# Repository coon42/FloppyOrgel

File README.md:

# FloppyOrgel
Collection of Software for the Floppy Orgel

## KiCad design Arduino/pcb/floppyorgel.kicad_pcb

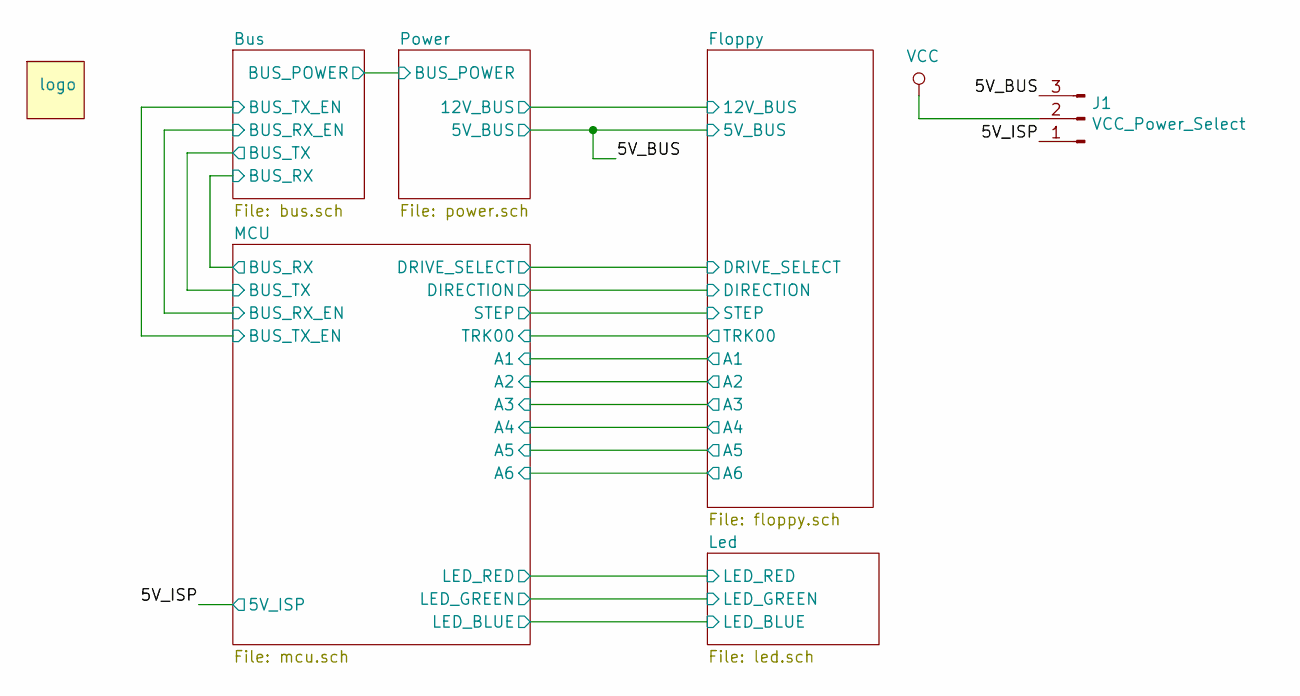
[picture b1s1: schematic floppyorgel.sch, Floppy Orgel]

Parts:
J1: VCC_Power_Select; switch_mmp122-r
L1: logo

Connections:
/5V_BUS: J1.3; also elsewhere on the board
/5V_ISP: J1.1; also elsewhere on the board
VCC: J1.2; also elsewhere on the board

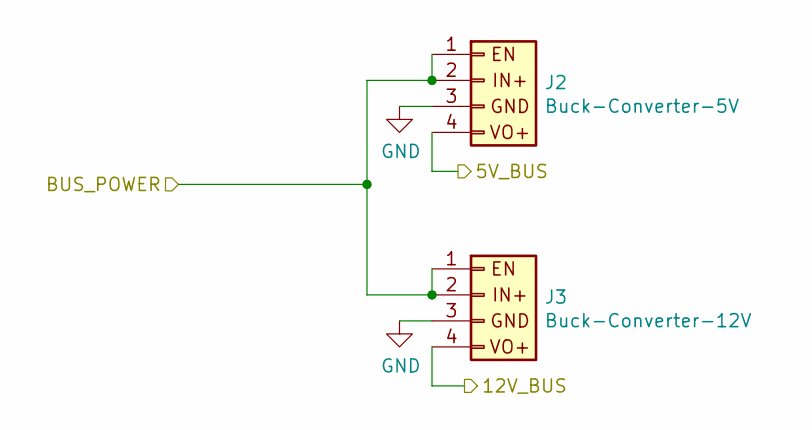
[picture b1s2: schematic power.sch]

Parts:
J2: Buck-Converter-5V; PinSocket_1x04_P2.54mm_Vertical
J3: Buck-Converter-12V; PinSocket_1x04_P2.54mm_Vertical

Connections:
/5V_BUS: J2.4; also elsewhere on the board
/Bus/BUS_POWER: J2.1, J2.2, J3.1, J3.2; also elsewhere on the board
/Floppy/12V_BUS: J3.4; also elsewhere on the board
GND: J2.3, J3.3; also elsewhere on the board

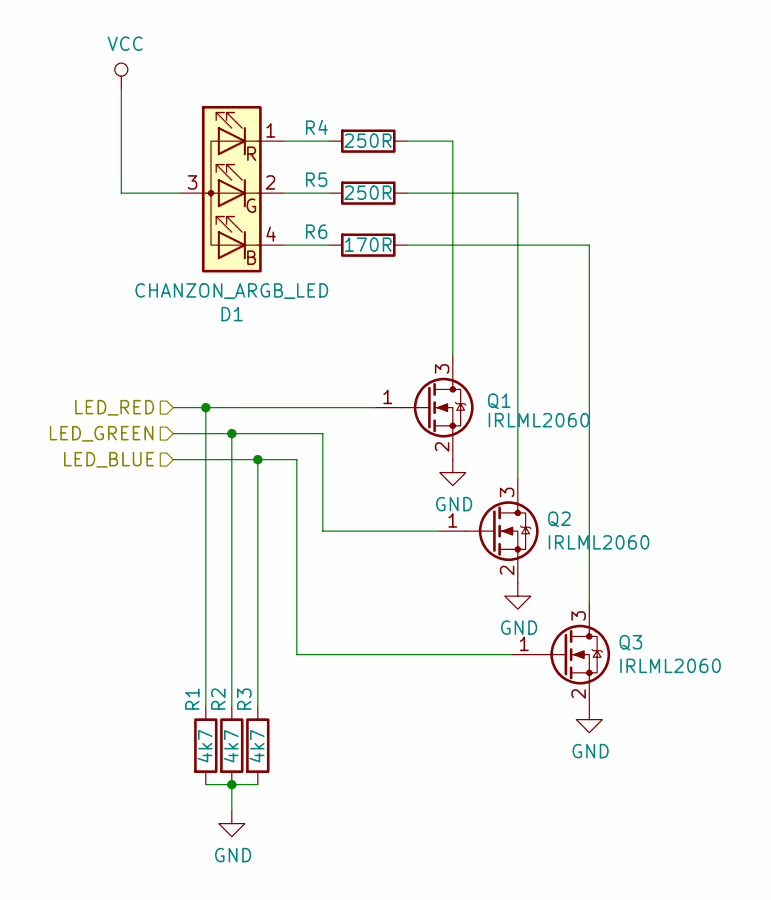
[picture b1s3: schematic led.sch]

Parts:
D1: CHANZON_ARGB_LED; rgb_led_0805_2012Metric
Q1, Q2, Q3: IRLML2060; SOT-23
R1, R2, R3: 4k7; R_0805_2012Metric
R4, R5: 250R; R_0805_2012Metric
R6: 170R; R_0805_2012Metric

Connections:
/Led/LED_BLUE: Q3.1 (G), R3.1; also elsewhere on the board
/Led/LED_GREEN: Q2.1 (G), R2.1; also elsewhere on the board
/Led/LED_RED: Q1.1 (G), R1.1; also elsewhere on the board
GND: Q1.2 (S), Q2.2 (S), Q3.2 (S), R1.2, R2.2, R3.2; also elsewhere on the board
unnamed: D1.1 (RK), R4.2
unnamed: D1.2 (GK), R5.2
unnamed: D1.4 (BK), R6.2
unnamed: Q1.3 (D), R4.1
unnamed: Q2.3 (D), R5.1
unnamed: Q3.3 (D), R6.1
VCC: D1.3 (COM); also elsewhere on the board

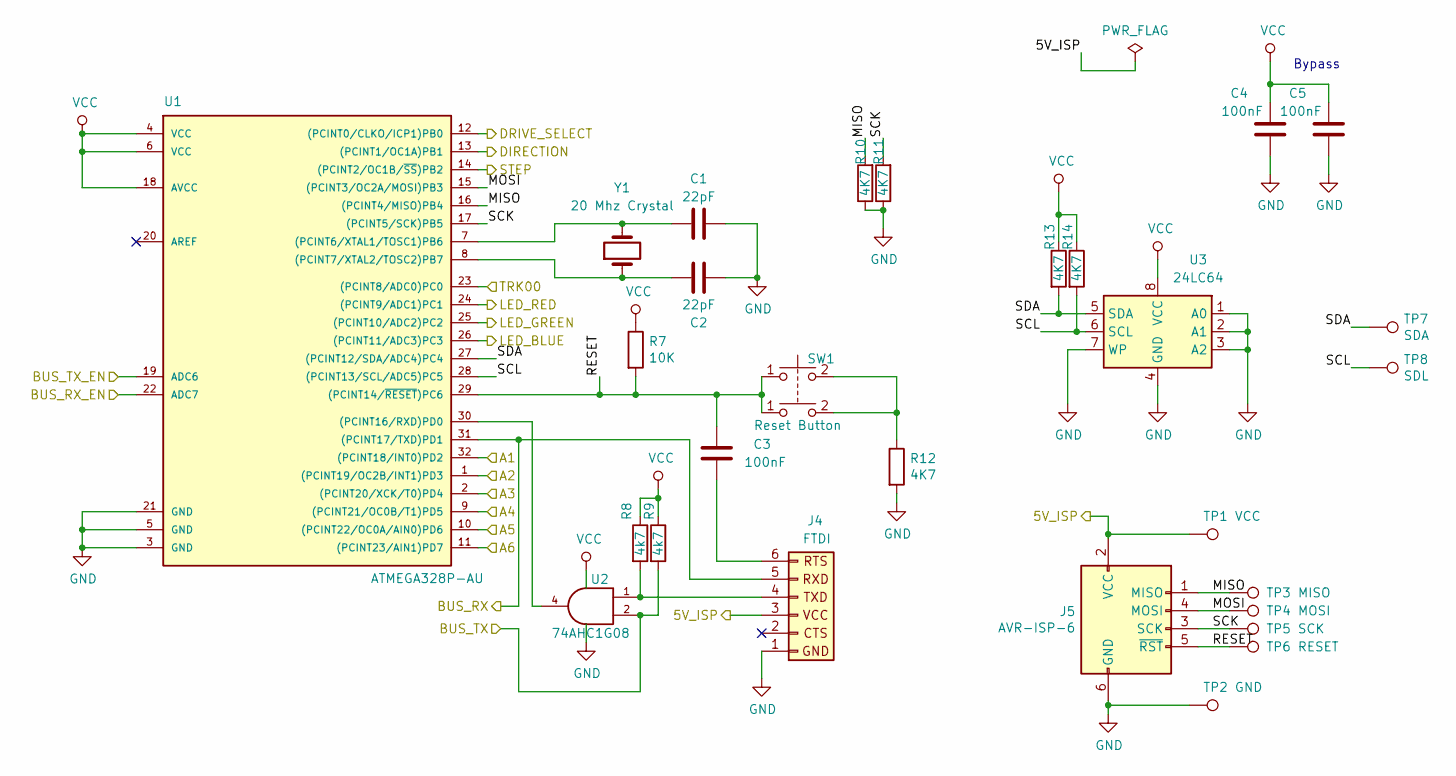
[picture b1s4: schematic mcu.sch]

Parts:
C1, C2: 22pF; C_0805_2012Metric
C3, C4, C5: 100nF; C_0805_2012Metric
J4: FTDI; PinHeader_1x06_P2.54mm_Vertical
J5: AVR-ISP-6; PinHeader_2x03_P2.54mm_Vertical
R7: 10K; R_0805_2012Metric
R8, R9: 4k7; R_0805_2012Metric
R10, R11, R12, R13, R14: 4K7; R_0805_2012Metric
SW1: Reset Button; SW_PUSH_6mm
TP1: VCC; TestPoint_Pad_D1.0mm
TP2: GND; TestPoint_Pad_D1.0mm
TP3: MISO; TestPoint_Pad_D1.0mm
TP4: MOSI; TestPoint_Pad_D1.0mm
TP5: SCK; TestPoint_Pad_D1.0mm
TP6: RESET; TestPoint_Pad_D1.0mm
TP7: SDA; TestPoint_Pad_D1.0mm
TP8: SDL; TestPoint_Pad_D1.0mm
U1: ATMEGA328P-AU; LQFP-32_7x7mm_P0.8mm
U2: 74AHC1G08; SOT-23-5
U3: 24LC64; TSSOP-8_4.4x3mm_P0.65mm
Y1: 20 Mhz Crystal; Crystal_HC49-4H_Vertical

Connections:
/5V_ISP: J4.3 (VCC), J5.2 (VCC), TP1.1; also elsewhere on the board
/Bus/BUS_RX: J4.5 (Receive), U1.31 ((PCINT17/TXD)PD1); also elsewhere on the board
/Bus/BUS_RX_EN: U1.22 (ADC7); also elsewhere on the board
/Bus/BUS_TX: R9.2, U2.2; also elsewhere on the board
/Bus/BUS_TX_EN: U1.19 (ADC6); also elsewhere on the board
/Floppy/A1: U1.32 ((PCINT18/INT0)PD2); also elsewhere on the board
/Floppy/A2: U1.1 ((PCINT19/OC2B/INT1)PD3); also elsewhere on the board
/Floppy/A3: U1.2 ((PCINT20/XCK/T0)PD4); also elsewhere on the board
/Floppy/A4: U1.9 ((PCINT21/OC0B/T1)PD5); also elsewhere on the board
/Floppy/A5: U1.10 ((PCINT22/OC0A/AIN0)PD6); also elsewhere on the board
/Floppy/A6: U1.11 ((PCINT23/AIN1)PD7); also elsewhere on the board
/Floppy/DIRECTION: U1.13 ((PCINT1/OC1A)PB1); also elsewhere on the board
/Floppy/DRIVE_SELECT: U1.12 ((PCINT0/CLKO/ICP1)PB0); also elsewhere on the board
/Floppy/STEP: U1.14 ((PCINT2/OC1B/~SS~)PB2); also elsewhere on the board
/Floppy/TRK00: U1.23 ((PCINT8/ADC0)PC0); also elsewhere on the board
/Led/LED_BLUE: U1.26 ((PCINT11/ADC3)PC3); also elsewhere on the board
/Led/LED_GREEN: U1.25 ((PCINT10/ADC2)PC2); also elsewhere on the board
/Led/LED_RED: U1.24 ((PCINT9/ADC1)PC1); also elsewhere on the board
/MCU/MISO: J5.1 (MISO), R10.2, TP3.1, U1.16 ((PCINT4/MISO)PB4)
/MCU/MOSI: J5.4 (MOSI), TP4.1, U1.15 ((PCINT3/OC2A/MOSI)PB3)
/MCU/RESET: C3.1, J5.5 (~RST), R7.2, SW1.1, TP6.1, U1.29 ((PCINT14/~RESET~)PC6)
/MCU/SCK: J5.3 (SCK), R11.2, TP5.1, U1.17 ((PCINT5/SCK)PB5)
/MCU/SCL: R14.2, TP8.1, U1.28 ((PCINT13/SCL/ADC5)PC5), U3.6 (SCL)
/MCU/SDA: R13.2, TP7.1, U1.27 ((PCINT12/SDA/ADC4)PC4), U3.5 (SDA)
GND: C1.2, C2.1, C4.2, C5.2, J4.1 (Ground), J5.6 (GND), R10.1, R11.1, R12.2, TP2.1, U1.3 (GND), U1.5 (GND), U1.21 (GND), U2.3 (GND), U3.1 (A0), U3.2 (A1), U3.3 (A2), U3.4 (GND), U3.7 (WP); also elsewhere on the board
unnamed: C1.1, U1.7 ((PCINT6/XTAL1/TOSC1)PB6), Y1.2
unnamed: C2.2, U1.8 ((PCINT7/XTAL2/TOSC2)PB7), Y1.1
unnamed: C3.2, J4.6 (Ready_to_send)
unnamed: J4.4 (Transmit), R8.2, U2.1
unnamed: R12.1, SW1.2
unnamed: U1.30 ((PCINT16/RXD)PD0), U2.4
VCC: C4.1, C5.1, R7.1, R8.1, R9.1, R13.1, R14.1, U1.4 (VCC), U1.6 (VCC), U1.18 (AVCC), U2.5 (VCC), U3.8 (VCC); also elsewhere on the board

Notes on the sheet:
Bypass

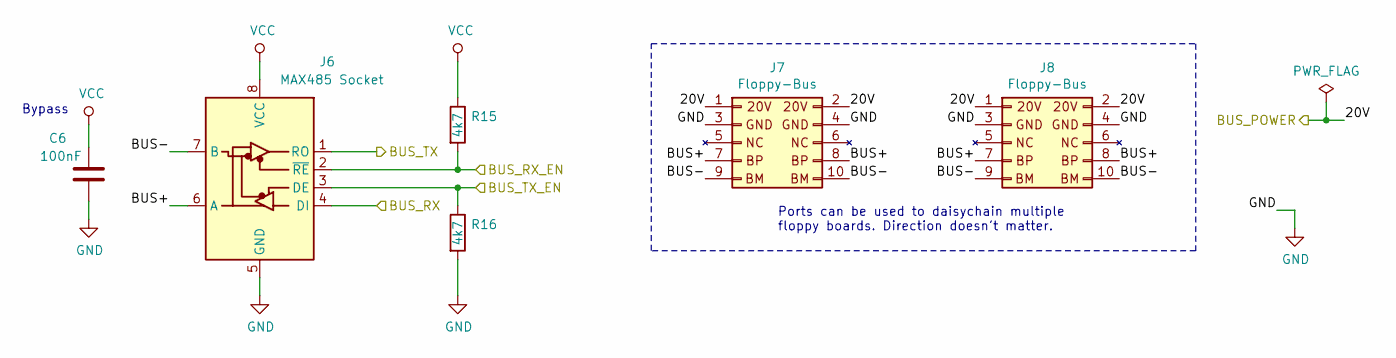
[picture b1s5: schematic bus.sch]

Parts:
C6: 100nF; C_0805_2012Metric
J6: MAX485 Socket; dil_8-300_socket
J7, J8: Floppy-Bus; Shrouded_Header_2x05_Pitch2.54mm
R15, R16: 4k7; R_0805_2012Metric

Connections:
/Bus/BUS+: J6.6 (A), J7.7 (BM), J7.8 (BM), J8.7 (BM), J8.8 (BM)
/Bus/BUS-: J6.7 (B), J7.9, J7.10, J8.9, J8.10
/Bus/BUS_POWER: J7.1 (20V), J7.2 (20V), J8.1 (20V), J8.2 (20V); also elsewhere on the board
/Bus/BUS_RX: J6.4 (DI); also elsewhere on the board
/Bus/BUS_RX_EN: J6.2 (~RE), R15.2; also elsewhere on the board
/Bus/BUS_TX: J6.1 (RO); also elsewhere on the board
/Bus/BUS_TX_EN: J6.3 (DE), R16.1; also elsewhere on the board
GND: C6.2, J6.5 (GND), J7.3 (GND), J7.4 (GND), J8.3 (GND), J8.4 (GND), R16.2; also elsewhere on the board
VCC: C6.1, J6.8 (VCC), R15.1; also elsewhere on the board

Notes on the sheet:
Bypass
Ports can be used to daisychain multiple floppy boards. Direction doesn't matter.

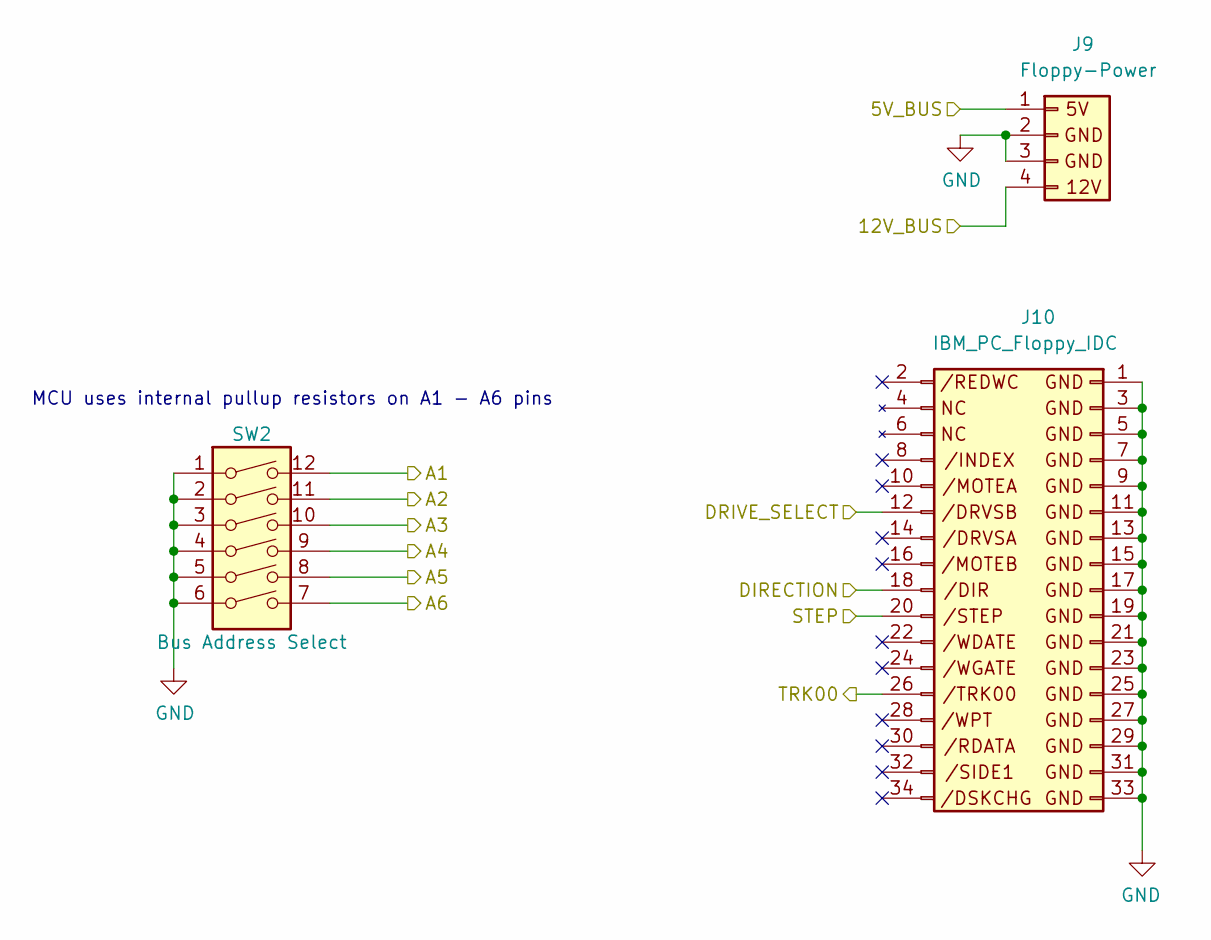
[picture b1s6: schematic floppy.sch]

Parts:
J9: Floppy-Power; Floppy_Power_1x04_Pitch2.54mm
J10: IBM_PC_Floppy_IDC; ibm_pc_floppy_idc
SW2: Bus Address Select; SW_DIP_SPSTx06_Slide_9.78x17.42mm_W7.62mm_P2.54mm

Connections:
/5V_BUS: J9.1 (5V); also elsewhere on the board
/Floppy/12V_BUS: J9.4 (12V); also elsewhere on the board
/Floppy/A1: SW2.12; also elsewhere on the board
/Floppy/A2: SW2.11; also elsewhere on the board
/Floppy/A3: SW2.10; also elsewhere on the board
/Floppy/A4: SW2.9; also elsewhere on the board
/Floppy/A5: SW2.8; also elsewhere on the board
/Floppy/A6: SW2.7; also elsewhere on the board
/Floppy/DIRECTION: J10.18; also elsewhere on the board
/Floppy/DRIVE_SELECT: J10.12; also elsewhere on the board
/Floppy/STEP: J10.20; also elsewhere on the board
/Floppy/TRK00: J10.26; also elsewhere on the board
GND: J9.2 (Ground), J9.3 (Ground), J10.1, J10.3, J10.5, J10.7, J10.9, J10.11, J10.13, J10.15, J10.17, J10.19, J10.21, J10.23, J10.25, J10.27, J10.29, J10.31, J10.33, SW2.1, SW2.2, SW2.3, SW2.4, SW2.5, SW2.6; also elsewhere on the board

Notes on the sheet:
MCU uses internal pullup resistors on A1 - A6 pins

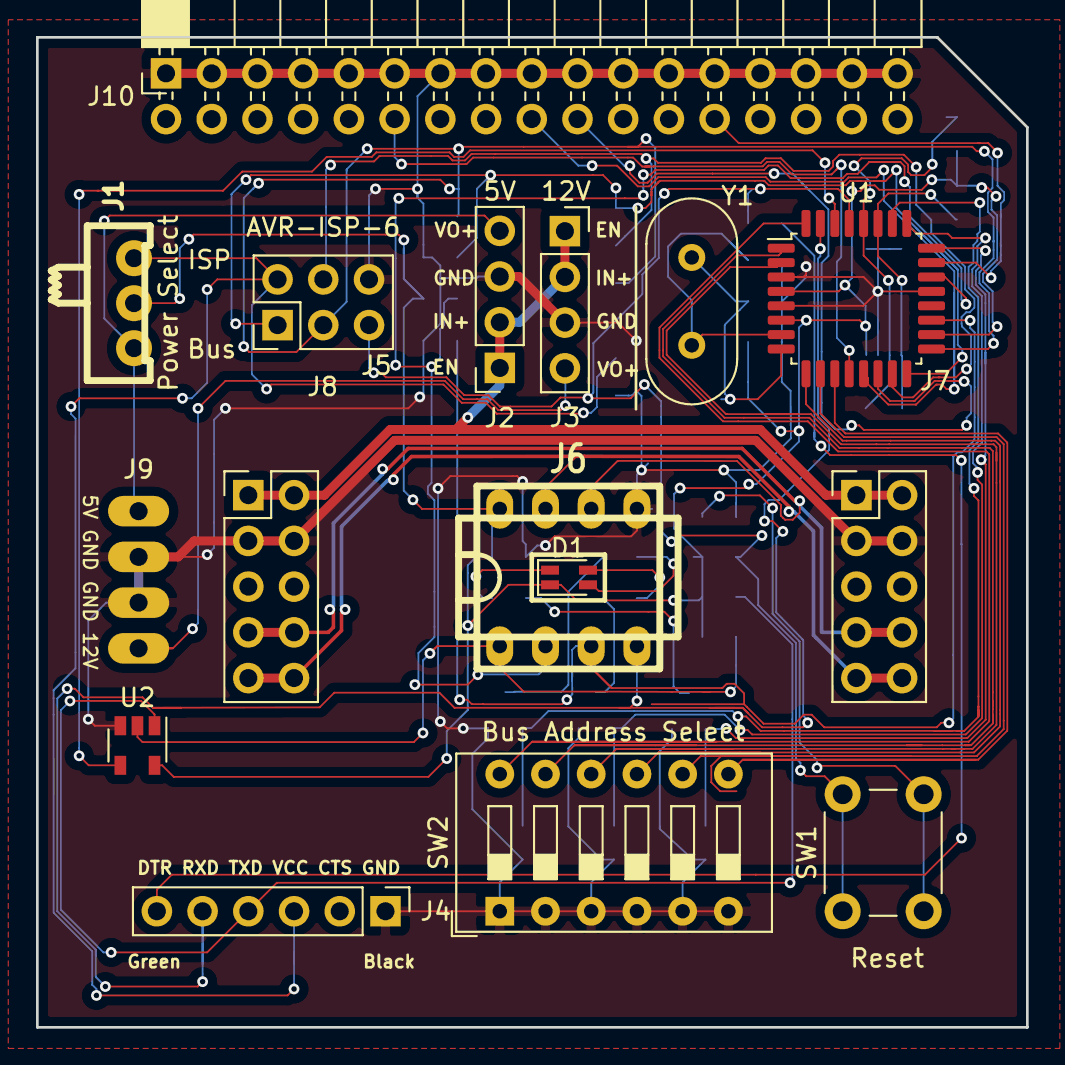
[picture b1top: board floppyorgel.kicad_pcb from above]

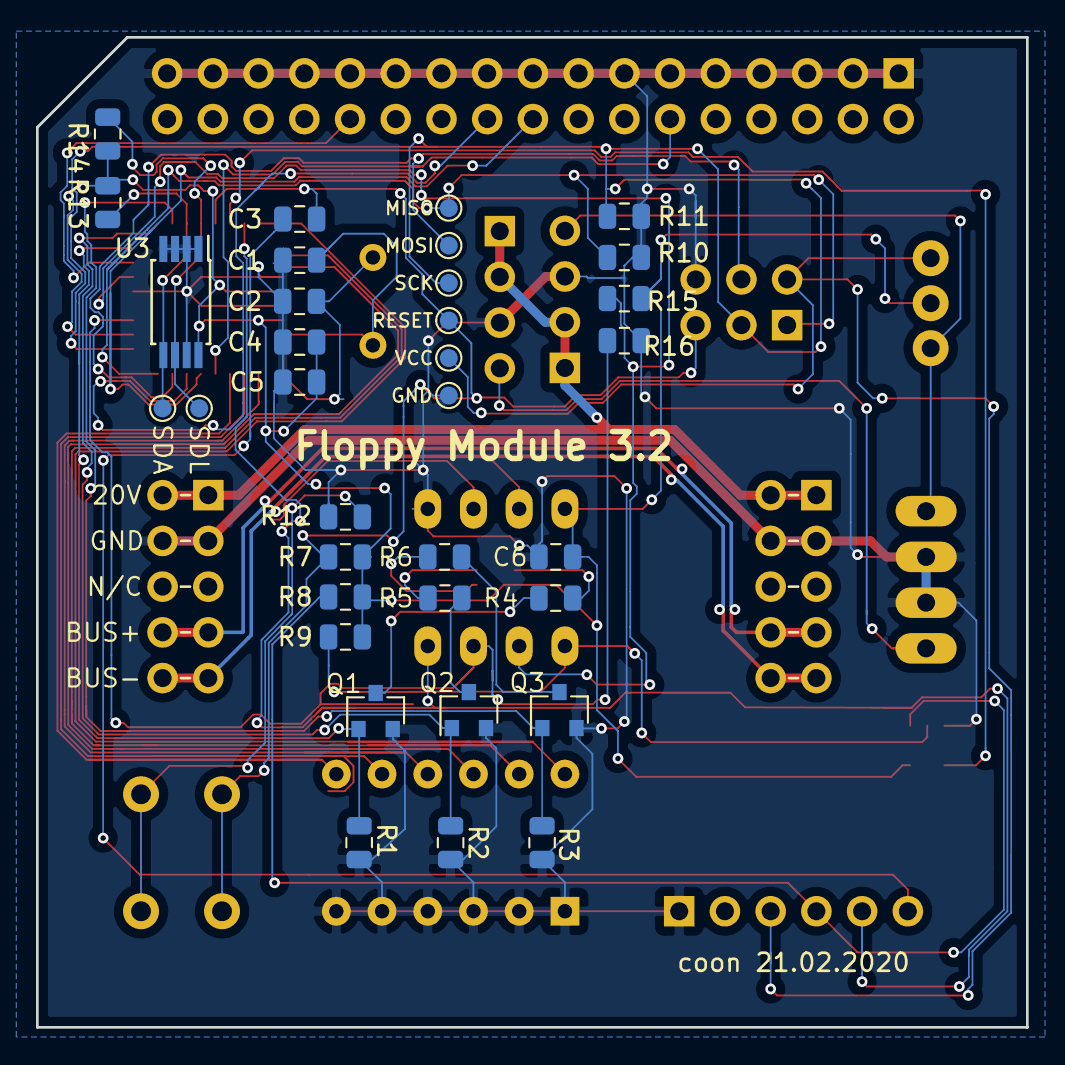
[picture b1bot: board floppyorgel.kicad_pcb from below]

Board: 2 copper layers, 55.0 x 55.0 mm, 51 parts (35 on the bottom side), 43 nets.

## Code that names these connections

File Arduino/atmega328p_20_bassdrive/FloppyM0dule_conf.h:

// Pin mappings
#define PIN_DRIVE_SELECT A0
#define PIN_DIRECTION       A1
#define PIN_STEP                   10 // PB2
#define PIN_TRACK_0            A5 // TOOD: use shift register for DIP switch and use other pin to keep I2C pins available!

#define PIN_RS485_DE      8 // PB0
#define PIN_RS485_NRE    9 // PB1

#define PIN_SHIFT_REGISTER_RCLK A2
#define PIN_UNDER_CHIP_LED A3

// Floppy settings
#define MAX_STEP_POSITION 70 // A floppy disk has 80 tracks (0 - 79). 
#define MAX_FREQUENCY 393 // TODO: Define per floppy drive and save into atmels flash chip?

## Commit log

2018-05-26 add FlyFi submodule + arduino firmware
2018-05-26 use proper subdirectory for arduino project
2018-05-26 replace FlyFi by FlyFi_cpp submodule
2018-05-26 Add Floppy-Music--midis- submodule + update FlyFi_cpp submodule
2018-05-27 update FlyFi_cpp submodule
2018-06-23 update subrepos
2018-06-25 Arduino: add provisional bassdrive sketch
2018-06-28 rename: pcb -> old_pcb
2018-06-28 arduino: do not turn on first led on boot
2018-06-28 arduino: add missing file for bassdrive
2018-07-04 pcb: add floppy_power footprint
2018-07-04 pcb: update
2019-02-24 pcb: add footprints subdir with some parts
2019-02-24 pcb: remove .bak files
2019-02-24 pcb: add 3d subdir
2019-02-24 pcb: add sym-lib-table
2019-02-24 pcb: add shrouded.pretty
2019-02-24 pcb: move floppy power footprint
2019-02-24 pcb: add floppy-power part
2019-02-24 pcb: add ibm_pc_floppy_idc part
2019-02-24 pcb: use new parts
2019-02-24 pcb: remove _saved_floppyorgel.sch
2019-02-24 pcb: fix footprint paths
2019-04-21 ibm_pc_floppy_idc.lib: make N/C pins not connected
2019-04-21 floppyorgel.sch: do some routing
2019-04-21 floppyorgel.sch: auto fix of error
2019-04-22 floppyorgel.sch: continue wiring up
2019-04-22 floppyorgel.sch: auto fix of error again
2019-04-22 floppyorgel.sch: wiring shift registers
2019-04-22 floppyorgel.sch: wiring reset circuit
2019-04-22 floppyorgel.sch: auto repair
2019-04-22 floppyorgel.sch: add bypass caps
2019-04-22 floppyorgel.sch: add hierachical sheets
2019-04-22 floppyorgel.sch: reduce ERC errors
2019-04-23 pcb: add vcc power select footprint
2019-04-23 pcb: continue wiring / move parts to hierachival sheets
2019-04-27 pcb: finish wiring / use ws2812 under chip led
2019-04-27 pcb: assign footprints
2019-05-03 pcb: add I2C eeprom
2019-05-03 pcb: finished part placement
2019-05-04 pcb: add SOIC-8 socket footprint + 3D model
2019-05-05 pcb: continue placement + add some info on silk
2019-05-08 pcb: add testpads for SPI
2019-05-10 pcb: add testpads for I2C
2019-05-11 pcb: fix bus wiring, add bus silk pin descriptions
2019-05-17 pcb: add logo and zones
2019-05-17 pcb: add led series resistors to rgb led
2019-05-18 pcb: add missing footprints / add component for logo footprint
2019-05-18 pcb: fix logo library
2019-05-18 pcb: add customized footprint for floppy connector
2019-05-18 pcb: fix FTDI and floppy connector orientation
2019-05-18 pcb: add 'ThinkPad' font
2019-05-18 pcb: add mosfets to RGB led
2019-05-23 pcb: add footprint for RGB led
2019-06-01 pcb: add switch for VCC power select
2019-06-01 pcb: add footprint + 3D model for switch
2019-06-01 pcb: cut floppy edge + beautification
2019-06-03 pcb: some routing
2019-06-04 pcb: add rgb_led symbol
2019-06-04 pcb: fix rgb led footprint
2019-06-04 pcb: add rgb led datasheet
2019-07-17 pcb: finished routing
2019-08-11 pcb: minor adjustments in silkscreen
2019-08-18 pcb: further adjustments in silkscreen
2019-08-29 pcb: swap red and blue pin on RGB led
2019-09-10 pcb: mcu: add image for 328p TQFP pinout
2019-09-10 pcb: mcu: add and route I2C pull up resistors
2019-10-02 firmware: add firmware for revision 3.x boards
2019-10-02 pcb: use OR gate between FTDI and RS485 TX lines
2019-10-02 pcb: bus: more descriptive text for bus connectors
2019-10-03 pcb: mcu: replace OR by AND gate / use pullups on TX pins
2019-10-03 pcb: mcu / bus: improve TX/RX labels for RS485 transceiver
2019-10-04 pcb: did... something
2019-10-05 pcb / floppy: remove 4094 shift register / connect address connector directly
2019-10-05 pcb / led: remove hc595 shift register / connect led directly
2019-10-10 pcb: route RS485 control pins
2019-10-16 pcb: do some final optimizations for v3.1
2020-02-15 migrate to kicad 5.x
2020-02-15 pcb: increase board dimensions by 5x5mm + delete all tracks
2020-02-16 pcb: ajdust design rules (via size)
2020-02-16 pcb: begin routing for v3.2
2020-02-17 pcb: rename RS485 bus pins + differential pair routing
2020-02-18 pcb: more routing...
2020-02-21 pcb: continue routing
2020-02-21 pcb: finish routing of v3.2
2020-02-21 pcb: reannotate symbols
2020-02-22 fix routing with v3.2 with updated annotations
2022-05-26 add .gitignore
2022-05-26 fix footprints
